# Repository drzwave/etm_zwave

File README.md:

# etm\_zwave
Z-Wave Embedded Trace Module (ETM) debugging example code

The ETM is an invaluable tool for debugging embedded code and measuring code coverage in real-time.
More details on ETM can be found on the [ARM](https://developer.arm.com/documentation/ddi0337/h/embedded-trace-macrocell/about-the-etm) and [Segger](https://www.segger.com/) web sites.

The example code here is provided AS-IS and without warrantee.

# Setup

## Hardware

- Z-Wave Developers Kit - WSTK and a Radio board
    - Or your board assuming it has the JTrace pins
- [Segger J-Trace Pro](https://www.segger.com/products/debug-probes/j-trace/)
    - The Cortex-M model is sufficient for Z-Wave debug (the cheaper one)
    - Cables and power source
- J-Trace 20 pin connector pinout: 
    - 0.05" (1.27mm) spacing
- Connect the DUT to the J-Trace and ensure the Target Power is green
    - Note that the 20 pin debug cable should be as short as possible - ideally just 2-3"
    - If you get LTRACE invalid frame errors on the trace, the signal quality across the ribbon cable is probably not good.
    - Try lowering the clock speed, adjusting the timing in JTrace and that all ground pins are connected.

## JT2Mini Adapter

- See the [Adapter](./adapter/ReadMe.md) folder for the J-Trace to MiniSimplicity adapter.

## Software

- Simplicity Studio (for building the code)
- Segger [Ozone](https://www.segger.com/products/development-tools/ozone-j-link-debugger/]Debugger) (supports ETM trace)
    - SVD files for the respective EFR32 - see the SVD folder
- This repo contains JLink scripts and other files needed for tracing

# Step by Step Instructions

1. Clone this repo into your Z-Wave project
2. Build the project in SSv5
3. Open Ozone
4. Click on the New Project wizard and select the .AXF file for the project. Ozone will find the source code files via the .axf file.
5. Click on File-\>Edit Project file (opens the .jdebug file)
6. Add the following lines to the end of the OnProjectLoad section
    1. Project.SetOSPlugin("FreeRTOSPlugin\_ARM"); 
    1. For xG13 projects:
        1. Project.AddSvdFile ("$(ProjectDir)/etm\_zwave/svd/EFR32XG13XFULL.svd"); 
    1. For xG14 projects:
        1. Project.AddSvdFile ("$(ProjectDir)/etm\_zwave/svd/EFR32XG14XFULL.svd"); 
    1. For xG23 projects:
        1. Project.AddSvdFile ("$(ProjectDir)/etm\_zwave/svd/EFR32XG23A000F512GM40\_SEQ\_M33.svd"); 
    2. For modules (ZGM130,ZGM230), just use the base-SoC part which has the same internal registers which is what the .SVD defines
7. Scroll down to the BeforeTargetConnect section
    1. uncomment the call and the }
    2. Add ONE of the following lines that matches your Z-Wave chip :
        1. Project.SetJLinkScript("$(ProjectDir)/etm_zwave/ZGM130S_Traceconfig.JLinkScript"); 
        1. Project.SetJLinkScript("$(ProjectDir)/etm_zwave/ZG23_Traceconfig.JLinkScript"); 
8. Enable Tracing
    1. Tools-\>Trace Settings 
    2. Trace Source is Trace Pins
    3. CPU Frequency is 39MHz
    4. Trace Port Width is ideally 4 but if you have limited pinout, 2 or even 1 will work but will stall the CPU potentially altering the program flow
    5. Increase the Maximum Instruction Count to at least 100M
    6. Trace Timing should be default - the script alters the slew rate of the GPIOs which should be sufficient with a short cable
9. Click on View -\> Instruction Trace, Code Profile, Timeline and any other windows desired
10. Click on Download and Reset Program  
11. Review the console window and look for any errors
12. The DUT should stop at the beginning of Main() and there is data in the Timeline

# Software Project Recommendations

- Do not use -flto optimization when debugging. Link Time Optimization (LTO) mashes the code making Ozone unable to match the PC with the C source code.
- Recommend installing Z-Wave DEBUG in the SLC - This will set the -Og optimzation option which will make the code much easier to trace and debug but requires more FLASH.
    - In Simplicity Studio, click on the .slcp file for your project, then Software Components, then scroll down (or search) for Z-Wave Debug and click on it, then install it. Do NOT ship production code with Z-Wave Debug installed! Uninstall it for the final production release.
    - May also want to install Z-Wave Debug Print and uncomment the #define DEBUGPRINT in app.c. This also requires IO Stream and a UART. This enables print statements to help with debugging. The print statements are sent out the uart and are visible on the SSv5 console window.

# TroubleShooting

- Ozone will give all sorts of different errors that most often are caused by Signal Integrity issues
    - LTRACE (Time since start: 0.139 656, Thread=ETM1): Unknown trace data packet detected
    - No trace clock present, trace may not work correctly.
    - LTRACE (Time since start: 0.074 546, Thread=ETM1): Trace overflow detected. Trace packets may have been lost.
    - General flakeyness where restarting Ozone yields different errors or works sometimes but not all the time
- Signal Integrity of TRACECLK and TRACEDATA
    - Use short cables (less than 6")
    - Connect EVERY ground pin on the 20-pin header to the DUT if possible or add additional GND wires
    - View the TRACECLK and TRACEDATA pins on a good scope with good grounds
        - Adjust the slew rate of the EFR GPIO port to try to make the signals cleaner or sharper (See the .JLinkScript file for an example)
    - Adjust the timing in the J-Trace - Ozone - Trace Settings - Trace Timing
        - If the cable is short, the trace timing timing should not need to be adjusted as the EFR provides good setup/hold

# Reference Documents

- [Segger Wiki on xG21](https://wiki.segger.com/Silicon_Labs_EFR32xG21)
- [Segger Wiki on xG23](https://wiki.segger.com/Silicon_Labs_EFR32xG23)

# Contacts - Eric Ryherd - Author

- File an Issue to report a problem or make a suggestion.

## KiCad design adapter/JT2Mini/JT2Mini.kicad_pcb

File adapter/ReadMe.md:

# J-Trace 19 pin to 10-pin MiniSimplicity Adapter PCB

This folder contains the KiCAD database for a small PCB that
provides a solid connection from the 19 pin 0.05" header on the
Segger J-Trace to the Silicon Labs MiniSimplicity header.

The board is plugged directly into the J-Trace without a cable. Be VERY careful to align the pins correctly! 
The DUT is then typically connected with a Tag-Connect or a Minisimplicity ribbon cable.
The cable should be short - less than 1 foot. There is only a single ground pin. The data rate of the pins is 20MHz so a short cable is necessary to ensure signal integrity.
Additional ground wire(s) between the JT2Mini and DUT are recommended to improve signal integrity. The wires should be the same length as the Tag-Connect cable.

This board assumes the PTI pins are NOT wired to the MiniSimplicity header and the D1 and D2 trace pins are wired in their place.

Ordering the PCB from a proto PCB house like [OSH-Park](https://oshpark.com/) is cheap (less than $10 for 3!) and fast.

The PCB is easily hand-soldered as there are no active components. The connectors are a bit small so you do need decent soldering skills and perhaps a magnifying glass. 

# ZGx23 to MiniSimplicity Connections

Trace requires the TRACECLK and at least 1 TRACEDATA pin. Fortunately TRACEDATA0 is the SWO pin so it is already wired to the MiniSimplicity header. The JT2Mini adapter typically provides 2 data pins which works with minimal stalling of the CPU.
The typical connections to the MiniSimplicity header for use with this adapter are as follows:

| Name | Port Pin | ZG23 pin # | ZGM230 Pin # | MiniSimplicity Header | Comments |
| ---     | ---  | --- | --- | --- | --- |
| TRACECLK | PA04 | 29 | 16 | 9  | Trace Clock instead of PTISYNC |
| TRACED0  | PA03 | 28 | 15 | 6  | TRACEDATA0 also SWO |
| TRACED1  | PA05 | 30 | 17 | 10 | TRACEDATA1 instead of PTIDATA  |

This connection differs from the typical connections described in various Silabs datasheets as the Packet Trace (PTI) Interface pins are normally wired to pins 9 and 10. 
The PTI is normally used for the Zniffer however most Z-Wave debug uses a standalone Zniffer which is typically a USB stick. Trace is much more important for debugging than the Zniffer coming from the DUT.

# Gerbers

The JT2Mini-Gerbers.zip file contains the Gerber files for ordering the PCB from any prototype PCB manufacturer.
Some PCB houses (like OSHPark) accept the KiCAD files directly.

# Bill Of Materials (BOM)

1. J1 - 20 pin header - [CBEC224-1079B001C1AF](https://www.digikey.com/en/products/detail/greenconn/CBEC224-1079B001C1AF/16529509) - $2.34
2. J2 - 10 pin header - [3220-10-0300-00](https://www.digikey.com/en/products/detail/cnc-tech/3220-10-0300-00/3883266) - $0.78

Plus the PCB of course. A 2-pin GND jumper from the DUT to the JT2Mini is recommended for improved signal integrity.

# Schematic 

See the [Schematic](./JT2Mini/JT2MiniSchematic.pdf) PDF if you don't have KiCAD installed.

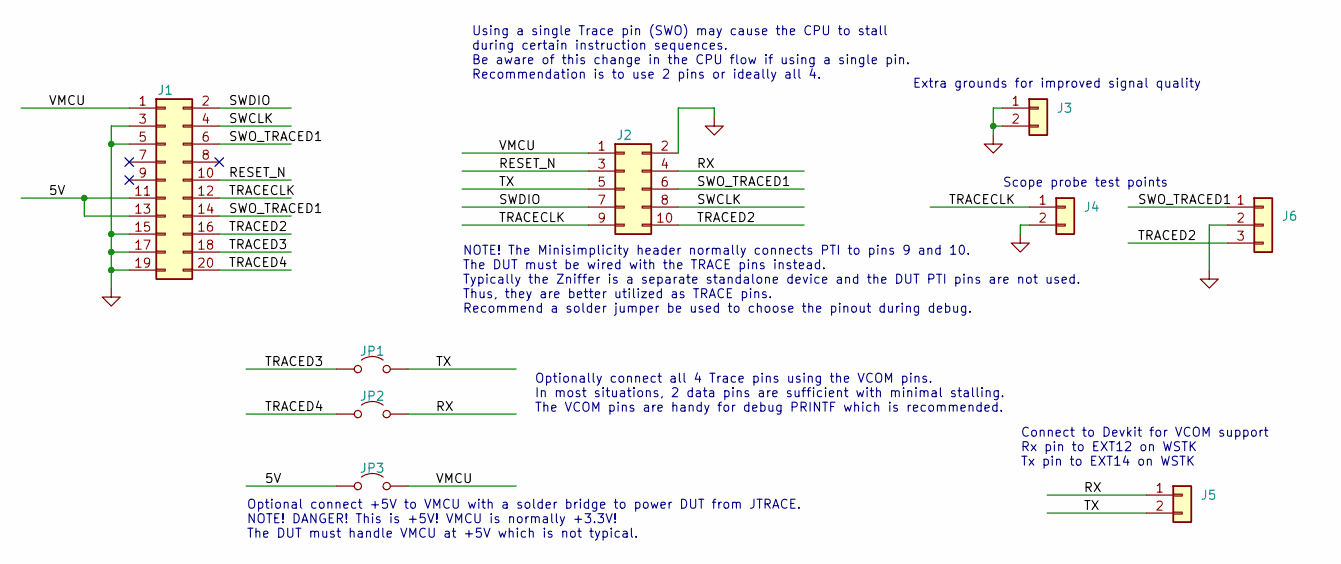
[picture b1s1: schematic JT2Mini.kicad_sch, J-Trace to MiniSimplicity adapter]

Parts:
J1: CBE224; PinHeader_2x10_P1.27mm_Greenconn
J2: 3220-10-0300-00; PinHeader_2x05_P1.27mm_Vertical_SMD
J3, J4, J5: Conn_01x02; PinHeader_1x02_P2.54mm_Vertical
J6: Conn_01x03; PinHeader_1x03_P2.54mm_Vertical
JP1, JP2, JP3: Jumper_2_Open; SolderJumper-2_P1.3mm_Open_RoundedPad1.0x1.5mm

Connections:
/5V: J1.11, J1.13, JP3.1 (A)
/RESET_N: J1.10, J2.3
/RX: J2.4, J5.1, JP2.2 (B)
/SWCLK: J1.4, J2.8
/SWDIO: J1.2, J2.7
/SWO_TRACED1: J1.6, J1.14, J2.6, J6.1
/TRACECLK: J1.12, J2.9, J4.1
/TRACED2: J1.16, J2.10, J6.3
/TRACED3: J1.18, JP1.1 (A)
/TRACED4: J1.20, JP2.1 (A)
/TX: J2.5, J5.2, JP1.2 (B)
/VMCU: J1.1, J2.1, JP3.2 (B)
GND: J1.3, J1.5, J1.15, J1.17, J1.19, J2.2, J3.1, J3.2, J4.2, J6.2

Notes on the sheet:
Optional connect +5V to VMCU with a solder bridge to power DUT from JTRACE. NOTE! DANGER! This is +5V! VMCU is normally +3.3V! The DUT must handle VMCU at +5V which is not typical.
NOTE! The Minisimplicity header normally connects PTI to pins 9 and 10. The DUT must be wired with the TRACE pins instead. Typically the Zniffer is a separate standalone device and the DUT PTI pins are not used. Thus, they are better utilized as TRACE pins. Recommend a solder jumper be used to choo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
Using a single Trace pin (SWO) may cause the CPU to stall during certain instruction sequences. Be aware of this change in the CPU flow if using a single pin. Recommendation is to use 2 pins or ideally all 4.
Connect to Devkit for VCOM support Rx pin to EXT12 on WSTK Tx pin to EXT14 on WSTK
Scope probe test points
Optionally connect all 4 Trace pins using the VCOM pins. In most situations, 2 data pins are sufficient with minimal stalling. The VCOM pins are handy for debug PRINTF which is recommended.
Extra grounds for improved signal quality

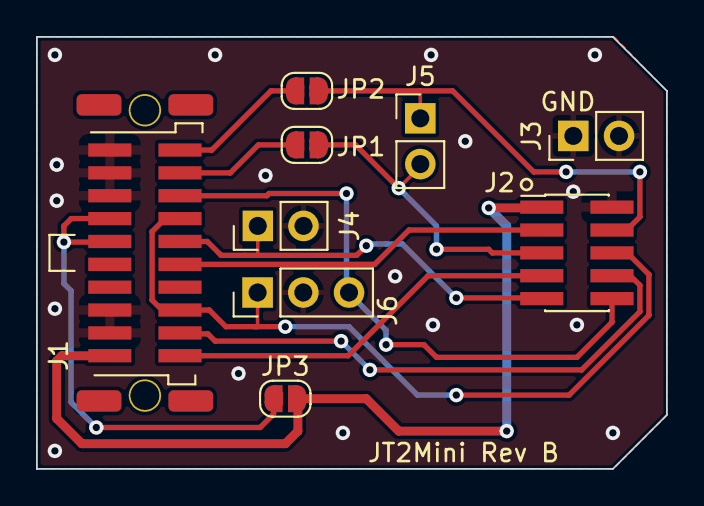
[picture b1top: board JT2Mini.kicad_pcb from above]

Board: 2 copper layers, 35.0 x 24.0 mm, 9 parts (0 on the bottom side), 13 nets.

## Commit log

2022-06-14 initial add of the code and updated ReadMe
2022-06-15 added .svd files, more docs
2022-06-15 Switch to using the JLinkScript instead of having to compile code into the project
2022-06-15 added 1st pass ZG23 script
2022-06-15 ZG23 improvements but not working yet.
2022-06-23 Trace is working on ZG23
2022-07-01 doubled the TRACECLK and increased Slew Rate for PortA - ETM is now DIV1 from the CPU and TRACECLK is 20MHz
2022-11-30 doc update
2023-03-30 trace with 2 or even just 1 pin is working.
2023-06-08 Added the J-Trace to Minisimplicity header adapter PCB
2023-06-26 Rev A PCB debugged - additional documentation
2023-06-26 fix the table
2023-07-12 Rev B PCB - added test points and GND for checking signal integrity
2024-04-19 minor tweaks
